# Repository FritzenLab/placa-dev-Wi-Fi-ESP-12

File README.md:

Placa de prototipagem Wi-Fi com ESP-12 (ESP8266)

TODA INFORMAÇÃO sobre esta placa de desenvolvimento Wi-FI ESP-12 está concentrada neste post do FritzenLab:
https://fritzenlab.com.br/2018/07/placa-de-desenvolvimento-wifi-esp12/ e aqui: 
https://fritzenlab.com.br/2016/03/wifi-esp12-esp8266-programando-com-a-ide-do-arduino/

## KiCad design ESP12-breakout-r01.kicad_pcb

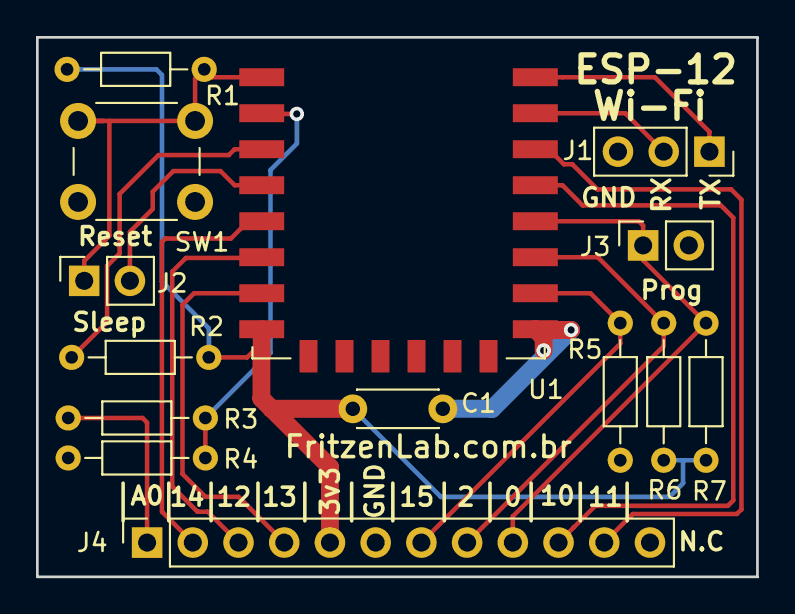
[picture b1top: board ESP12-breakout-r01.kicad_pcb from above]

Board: 2 copper layers, 40.0 x 30.0 mm, 14 parts (0 on the bottom side), 17 nets.

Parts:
C1: 100n; C_Disc_D4.3mm_W1.9mm_P5.00mm
J1: Conn_01x03_Male; PinSocket_1x03_P2.54mm_Vertical
J2, J3: Conn_01x02_Male; PinSocket_1x02_P2.54mm_Vertical
J4: Conn_01x12_Male; PinSocket_1x12_P2.54mm_Vertical
R1, R2, R3, R4, R5, R6, R7: R_US; R_Axial_DIN0204_L3.6mm_D1.6mm_P7.62mm_Horizontal
SW1: SW_Push; SW_PUSH_6mm
U1: ESP-12F; ESP-12E-clovis

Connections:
+3V3: C1.1, J4.5, R1.2, R2.1, R6.1, R7.1, U1.8
A0: J4.1, R3.1
Analog: R3.2, R4.1, U1.2
Enable: R2.2, U1.3
GND: C1.2, J1.3, J3.2, J4.6, R4.2, R5.1, SW1.1, U1.15
IO0: J3.1, J4.9, R7.2, U1.18
IO2: J4.8, R6.2, U1.17
IO4: J4.10, U1.19
IO5: J4.11, U1.20
IO12: J4.3, U1.6
IO13: J4.4, U1.7
IO14: J4.2, U1.5
IO15: J4.7, R5.2, U1.16
RX: J1.2, U1.21
Reset: J2.1, R1.1, SW1.2, U1.1
Sleep: J2.2, U1.4
TX: J1.1, U1.22

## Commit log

2018-07-28 primeiro commit
2018-07-28 adicionado esquematico
2018-07-28 criado read-me
    criado read-me
2018-07-29 alterado read-me
    alterado read-me
2019-03-05 revisão r01
    revisão r01, adicionados pinos ao conector de interface
